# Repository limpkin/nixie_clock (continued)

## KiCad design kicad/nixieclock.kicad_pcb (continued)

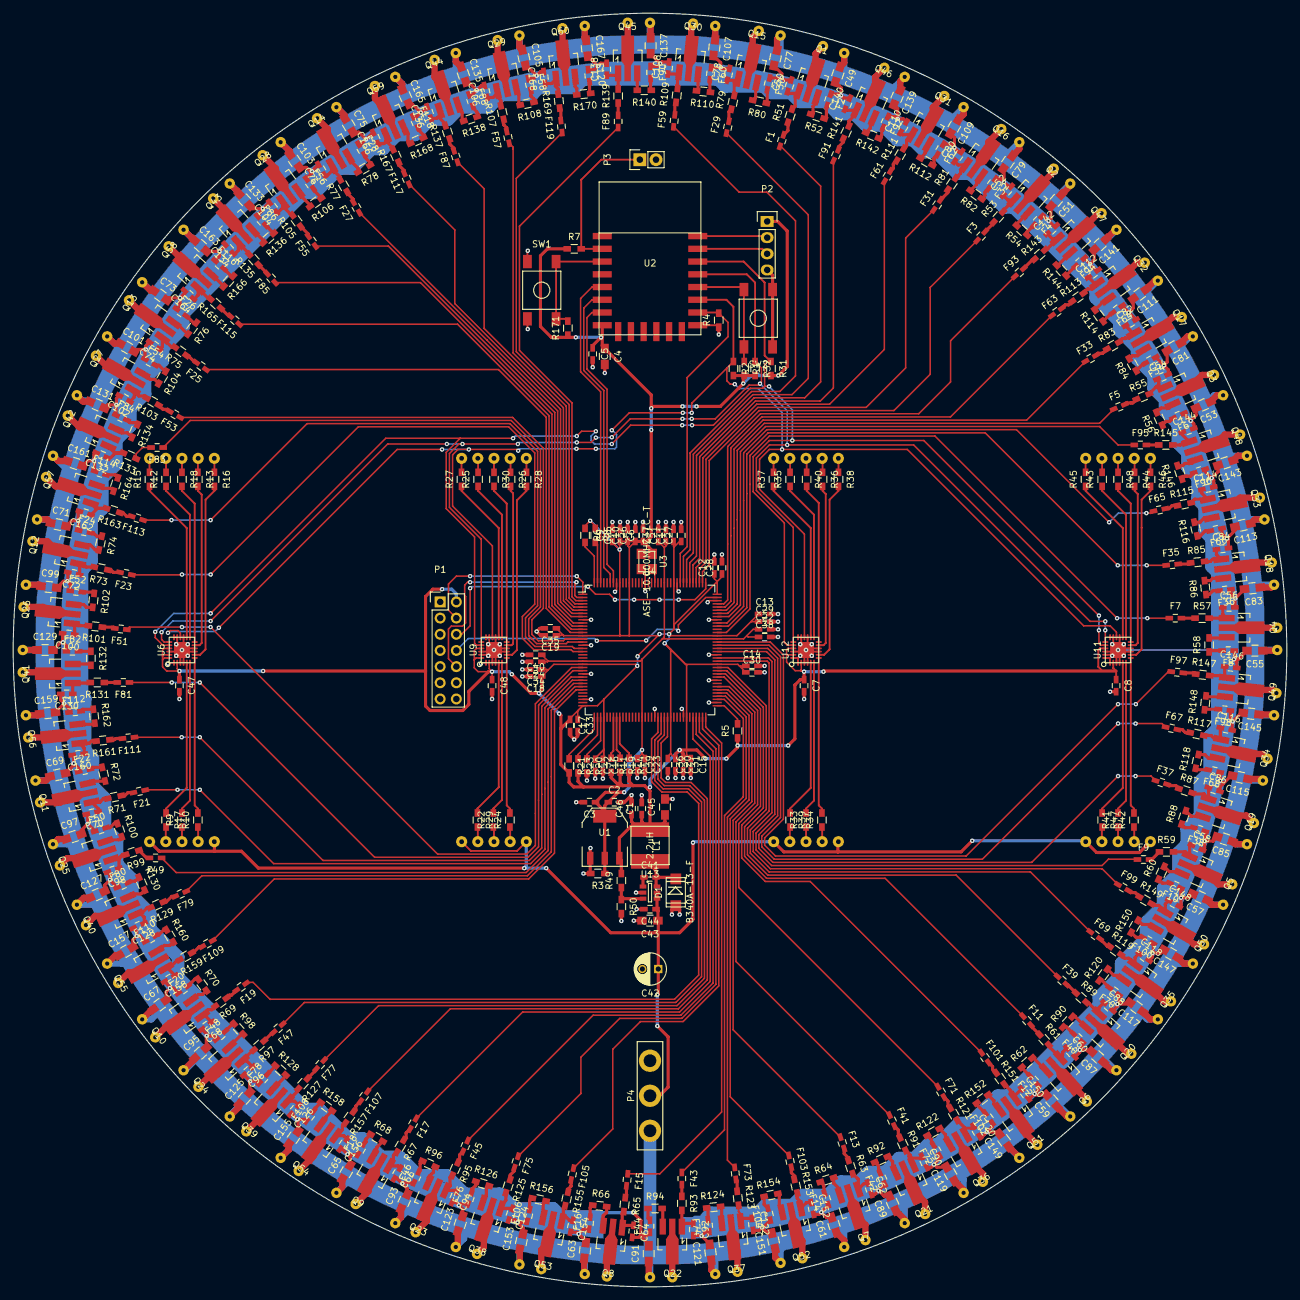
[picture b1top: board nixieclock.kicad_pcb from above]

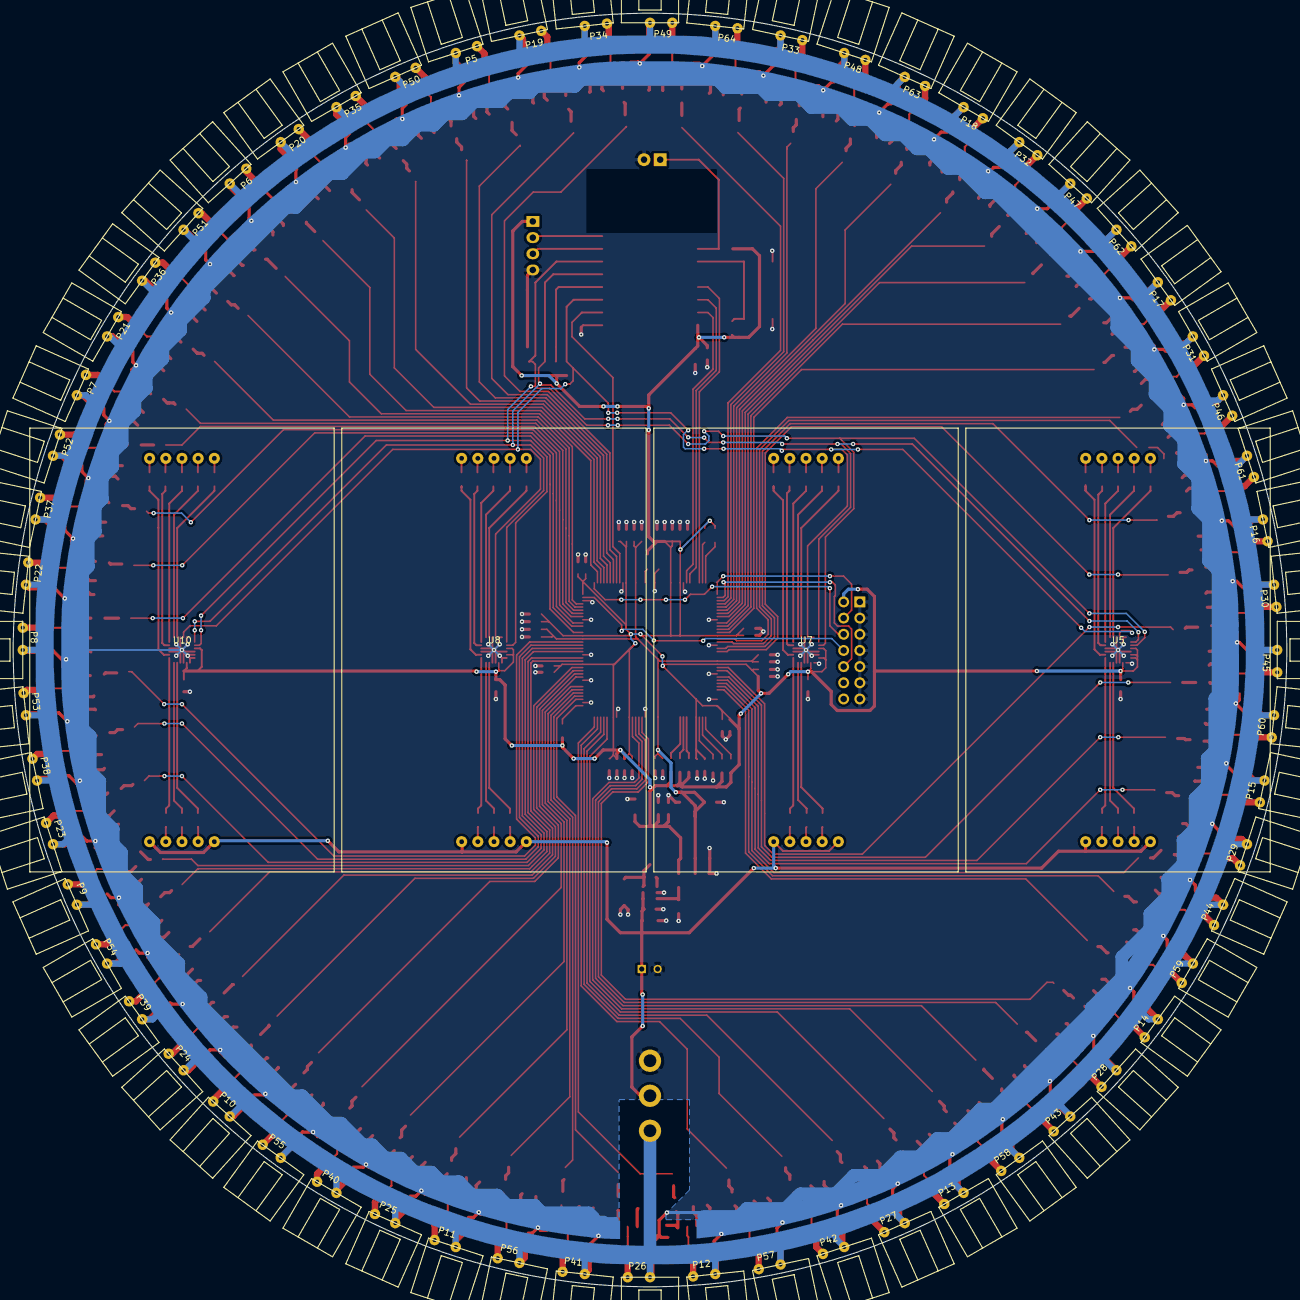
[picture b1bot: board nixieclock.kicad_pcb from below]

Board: 2 copper layers, 200.0 x 200.0 mm, 602 parts (66 on the bottom side), 458 nets.
